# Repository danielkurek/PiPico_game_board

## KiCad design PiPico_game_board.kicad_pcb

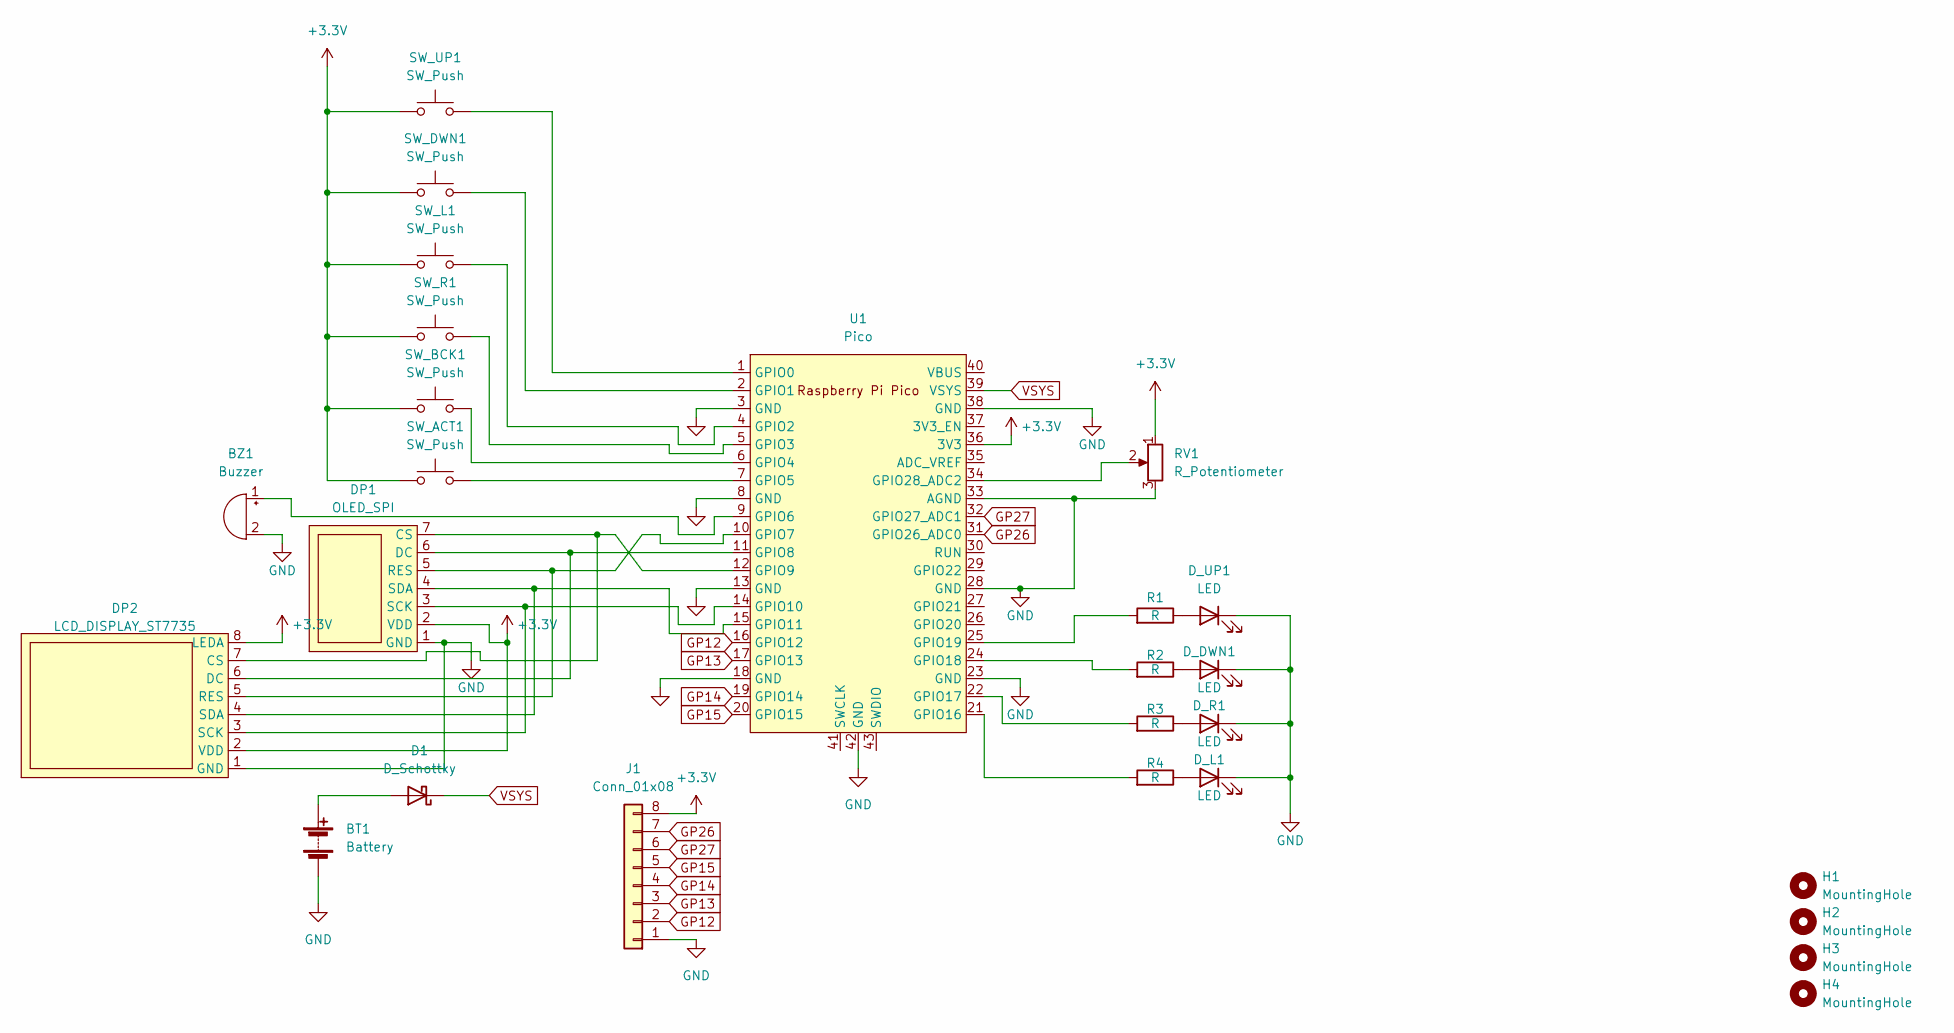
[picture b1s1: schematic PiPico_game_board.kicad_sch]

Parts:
BT1: Battery; BatteryWire-0.1sqmm_1x02_P3.6mm_D0.4mm_OD1mm_Relief2x_Back
BZ1: Buzzer; Buzzer_15x7.5RM7.6_12.2mm_Big_Pads_Back
D1: D_Schottky; D_DO-41_SOD81_P7.62mm_Horizontal_Big_Pads_Back
DP1: OLED_SPI; OLED_Display_Module
DP2: LCD_DISPLAY_ST7735; LCD_Display_1.77_Module
D_DWN1: LED; LED_D5.0mm_Big_Pads_Back
D_L1: LED; LED_D5.0mm_Big_Pads_Back
D_R1: LED; LED_D5.0mm_Big_Pads_Back
D_UP1: LED; LED_D5.0mm_Big_Pads_Back
H1, H2, H3, H4: MountingHole; MountingHole_2.2mm_M2
J1: Conn_01x08; PinHeader_1x08_P2.54mm_Vertical
R1, R2, R3, R4: R; R_easy_L6.3mm_D2.5mm_P10.16mm_Horizontal_Big_Pads_Back
RV1: R_Potentiometer; Potentiometer_Piher_PT-10-V10_Vertical_Hole
SW_ACT1: SW_Push; SW_PUSH_6mm_Back
SW_BCK1: SW_Push; SW_PUSH_6mm_Back
SW_DWN1: SW_Push; SW_PUSH-12mm_Omron_Back
SW_L1: SW_Push; SW_PUSH-12mm_Omron_Back
SW_R1: SW_Push; SW_PUSH-12mm_Omron_Back
SW_UP1: SW_Push; SW_PUSH-12mm_Omron_Back
U1: Pico; RPi_Pico_SMD_TH

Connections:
+3V3: DP1.2 (VDD), DP2.2 (VDD), DP2.8 (LEDA), J1.8, RV1.1, SW_ACT1.1, SW_BCK1.1, SW_DWN1.1, SW_L1.1, SW_R1.1, SW_UP1.1, U1.36 (3V3)
GND: BT1.2 (-), BZ1.2 (+), DP1.1 (GND), DP2.1 (GND), D_DWN1.1 (K), D_L1.1 (K), D_R1.1 (K), D_UP1.1 (K), J1.1, RV1.3, U1.3 (GND), U1.8 (GND), U1.13 (GND), U1.18 (GND), U1.23 (GND), U1.28 (GND), U1.33 (AGND), U1.38 (GND), U1.42 (GND)
GP12: J1.2, U1.16 (GPIO12)
GP13: J1.3, U1.17 (GPIO13)
GP14: J1.4, U1.19 (GPIO14)
GP15: J1.5, U1.20 (GPIO15)
GP26: J1.7, U1.31 (GPIO26_ADC0)
GP27: J1.6, U1.32 (GPIO27_ADC1)
unnamed: BT1.1 (+), D1.2 (A)
unnamed: BZ1.1 (-), U1.9 (GPIO6)
unnamed: DP1.3 (SCK), DP2.3 (SCK), U1.14 (GPIO10)
unnamed: DP1.4 (SDA), DP2.4 (SDA), U1.15 (GPIO11)
unnamed: DP1.5 (RES), DP2.5 (RES), U1.10 (GPIO7)
unnamed: DP1.6 (DC), DP2.6 (DC), U1.11 (GPIO8)
unnamed: DP1.7 (CS), DP2.7 (CS), U1.12 (GPIO9)
unnamed: D_DWN1.2 (A), R2.1
unnamed: D_L1.2 (A), R4.1
unnamed: D_R1.2 (A), R3.1
unnamed: D_UP1.2 (A), R1.1
unnamed: R1.2, U1.25 (GPIO19)
unnamed: R2.2, U1.24 (GPIO18)
unnamed: R3.2, U1.22 (GPIO17)
unnamed: R4.2, U1.21 (GPIO16)
unnamed: RV1.2, U1.34 (GPIO28_ADC2)
unnamed: SW_ACT1.2, U1.7 (GPIO5)
unnamed: SW_BCK1.2, U1.6 (GPIO4)
unnamed: SW_DWN1.2, U1.2 (GPIO1)
unnamed: SW_L1.2, U1.4 (GPIO2)
unnamed: SW_R1.2, U1.5 (GPIO3)
unnamed: SW_UP1.2, U1.1 (GPIO0)
VSYS: D1.1 (K), U1.39 (VSYS)

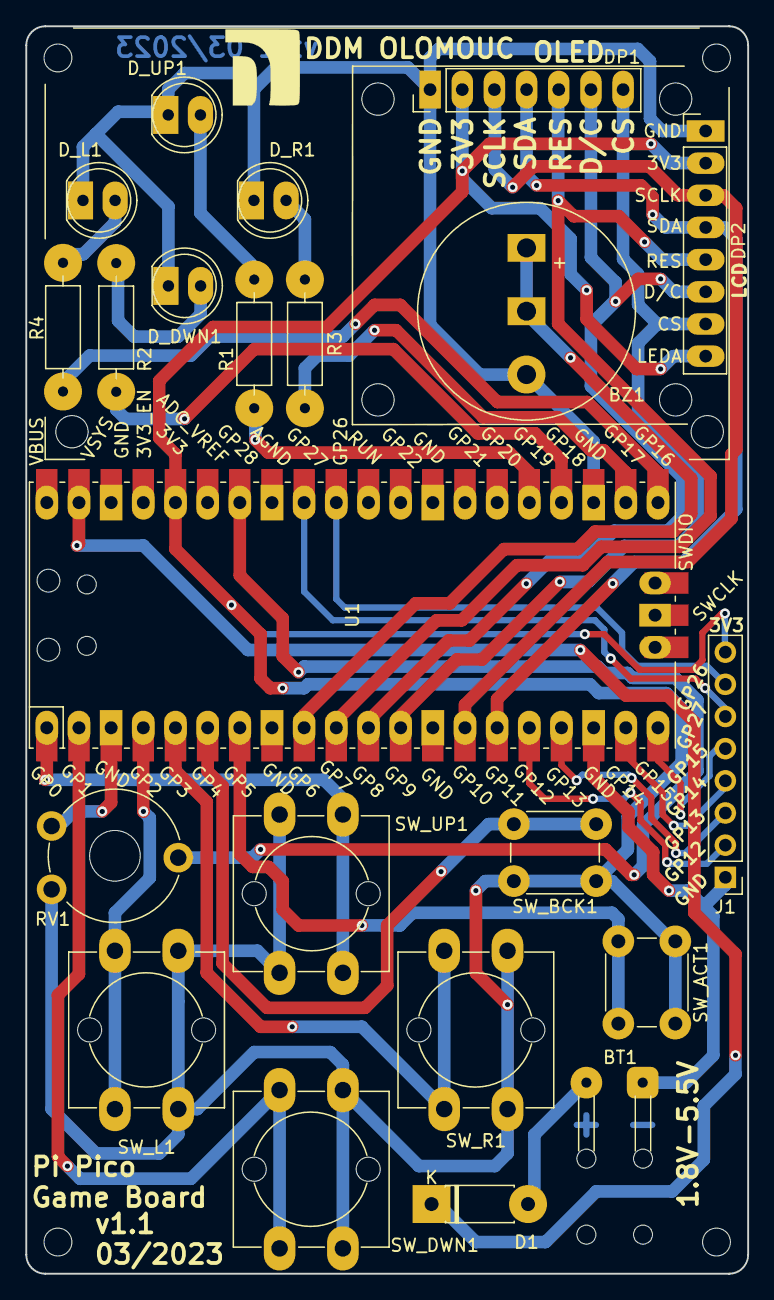
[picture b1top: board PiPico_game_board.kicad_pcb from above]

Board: 2 copper layers, 57.0 x 98.5 mm, 27 parts (0 on the bottom side), 31 nets.

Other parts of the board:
Ref**: Val**; DDM_06_F.SilkS

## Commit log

2022-03-14 Schematic v0.1
2022-03-17 Minor schematic changes
2022-04-11 External power + pcb change
    - external power source
    - mounting holes
    - buttons position changed
    - changed power for OLED from VSYS to 3V3
2022-04-22 Minor pcb routing changes
2022-07-17 Display support 3d model init
2022-07-18 display support clearance fix
2022-07-25 display support almost final
2022-07-26 backplate v1
2022-07-27 update clearances
2022-07-27 final design - backplate
2023-02-23 Fixed previous problems + support for LCD
